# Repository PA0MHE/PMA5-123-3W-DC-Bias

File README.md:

# PMA5-123-3W--DC-Bias

 DC bias PCB for PMA5-123-3W MMIC 3W 10GHz
 - ATtiny412 SW controlled
 - LDO for VDD, typical 7V
 - Switch to switch off or on Vdd
 - Idd Current measurment
 - DAC controlled (negative) Vgg powersupply
 - Inputs:
	+8 .. 12V DC
	PTT
 - Outputs
	Vdd
	Vgg (-1.5 .. -0.75V

# Key components:

	Attiny412
	MIC29302
	R05C1TF05S-R
	INA168

 # SW
	
	Uses megatinyCore in boardmanager
	Chip: ATtiny412
	clock: 8 MHz internal
	Programmer: serialUPDI 230400 baud

 By pressing SW1 during Power-Up, Idq is set to ~400mA and stored in EEPROM
 	
 HEX file is included.

# PCB

Gerber files are included, PCB's can be ordered at JCL PCB 

# Software

A V1.0 of the Control software is included.

# Disclaimer  

"This software and hardware design is provided "as is" and without  
any warranties, express or implied, including but not limited to the   
implied warranties of merchantability and fitness for a particular purpose." 
	
Normal operation:
During RX the Vgg is at around -1.5V and the Vdd is zero.
In TX the for 400mA Idq required bias voltage is applied at Vgg
	
First time use / calibration:
When SW1 is pressed during power up, the Idq is aligned at ~400mA, the required Vgg value is stored in non volatile memory.
When this above calibration is not done, the a Vgg minimum value of ~ -1.5V is always applied.

73's

Maarten PA0MHE, Rens PA3AXA

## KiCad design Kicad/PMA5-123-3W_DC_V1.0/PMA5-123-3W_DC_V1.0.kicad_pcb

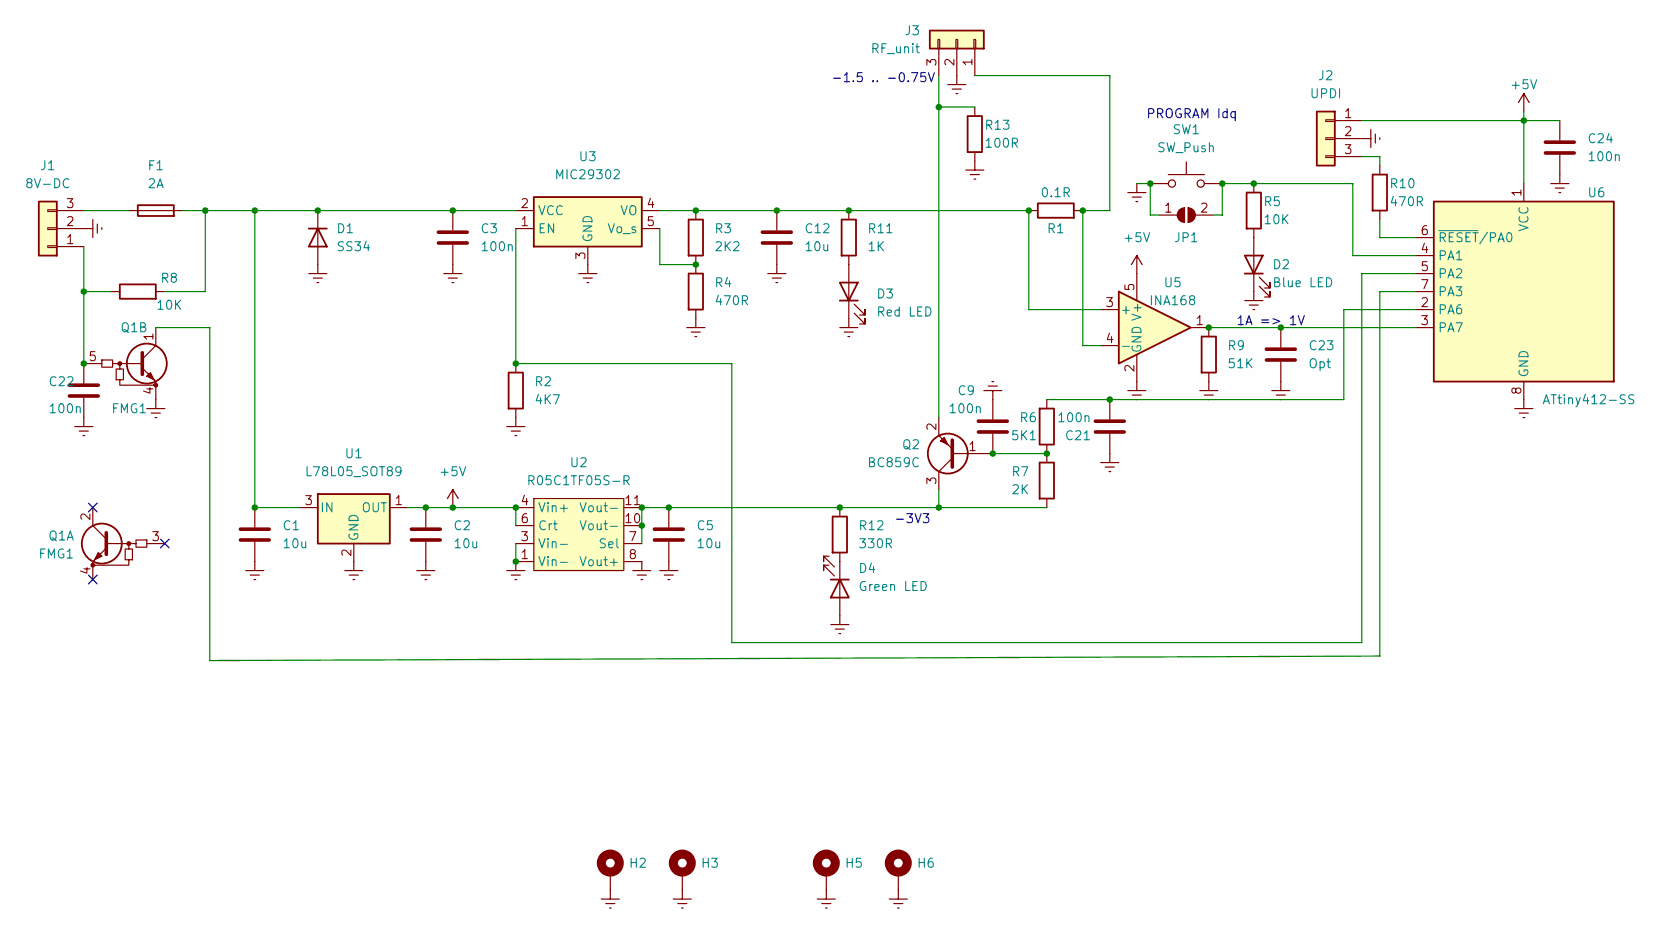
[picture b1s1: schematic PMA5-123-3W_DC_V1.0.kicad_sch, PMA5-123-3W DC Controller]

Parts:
C1: 10u; C_0805_2012Metric
C2, C5, C12: 10u; C_0603_1608Metric
C3, C9, C21, C22, C24: 100n; C_0603_1608Metric
C23: Opt; C_0603_1608Metric
D1: SS34; D_SMA; Mouser 750-SS34BF
D2: Blue LED; LED_0805_2012Metric
D3: Red LED; LED_0805_2012Metric
D4: Green LED; LED_0805_2012Metric
F1: 2A; Fuse_1812_4532Metric_Pad1.30x3.40mm_HandSolder; Mouser 576-1812L200/12DR
H2, H3, H5, H6: MountingHole_2.7mm_M2.5_Pad_Via
J1: 8V-DC; KF301-3P
J2: UPDI; PinHeader_1x03_P2.54mm_Vertical
J3: RF_unit; KF301-3P
JP1: '; SolderJumper-2_P1.3mm_Open_RoundedPad1.0x1.5mm
Q1: FMG1; SOT-25_HandSoldering; Mouser 755-FMG1AT148
Q2: BC859C; SOT-23
R1: 0.1R; R_2512_6332Metric; Mouser 603-PT2512FK-070R1L
R2: 4K7; R_0603_1608Metric
R3: 2K2; R_0603_1608Metric
R4, R10: 470R; R_0603_1608Metric
R5, R8: 10K; R_0603_1608Metric
R6: 5K1; R_0603_1608Metric
R7: 2K; R_0603_1608Metric
R9: 51K; R_0603_1608Metric
R11: 1K; R_0603_1608Metric
R12: 330R; R_0603_1608Metric
R13: 100R; R_0805_2012Metric
SW1: SW_Push; SW_SPST_FSMSM
U1: L78L05_SOT89; SOT-89-3; Mouser 511-L78L05ABU
U2: R05C1TF05S-R; R05C1TF05S; Mouser 919-R05C1TF05S-R
U3: MIC29302; TO-263-5_TabPin3; Mouser 998-MIC29302WU
U5: INA168; SOT-23-5; Mouser 595-INA168NA/3K
U6: ATtiny412-SS; SOIC-8_3.9x4.9mm_P1.27mm; Mouser 579-ATTINY412-SSF

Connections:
+5V: C2.1, C24.1, J2.1, U1.1 (OUT), U2.4 (Vin+), U2.5 (Vin+), U2.6 (Crt), U5.5 (V+), U6.1 (VCC)
GNDREF: C1.2, C2.2, C3.2, C5.2, C9.1, C12.2, C21.1, C22.2, C23.2, C24.2, D1.2 (A), D2.1 (K), D3.1 (K), D4.2 (A), H2.1, H3.1, H5.1, H6.1, J1.2, J2.2, J3.2, JP1.1 (A), Q1.4 (E1), R2.2, R4.2, R9.2, R13.2, SW1.1, U1.2 (GND), U2.1 (Vin-), U2.2 (Vin-), U2.3 (Vin-), U2.8 (Vout+), U2.9 (Vout+), U3.3 (GND), U5.2 (GND), U6.8 (GND)
unnamed: C1.1, C3.1, D1.1 (K), F1.2, R8.2, U1.3 (IN), U3.2 (VCC)
unnamed: C5.1, Q2.3 (C), R7.2, R12.1, U2.7 (Sel), U2.10 (Vout-), U2.11 (Vout-), U2.12 (Vout-)
unnamed: C9.2, Q2.1 (B), R6.1, R7.1
unnamed: C12.1, R1.1, R3.1, R11.1, U3.4 (VO), U5.3 (+)
unnamed: C21.2, R6.2, U6.2 (PA6)
unnamed: C22.1, J1.1, Q1.5 (B1), R8.1
unnamed: C23.1, R9.1, U5.1, U6.3 (PA7)
unnamed: D2.2 (A), R5.2
unnamed: D3.2 (A), R11.2
unnamed: D4.1 (K), R12.2
unnamed: F1.1, J1.3
unnamed: J2.3, R10.1
unnamed: J3.1, R1.2, U5.4 (-)
unnamed: J3.3, Q2.2 (E), R13.1
unnamed: JP1.2 (B), R5.1, SW1.2, U6.4 (PA1)
unnamed: Q1.1 (C1), U6.7 (PA3)
unnamed: R2.1, U3.1 (EN), U6.5 (PA2)
unnamed: R3.2, R4.1, U3.5 (Vo_s)
unnamed: R10.2, U6.6 (~RESET/PA0)

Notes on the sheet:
PROGRAM Idq
-3V3
-1.5 .. -0.75V
1A => 1V

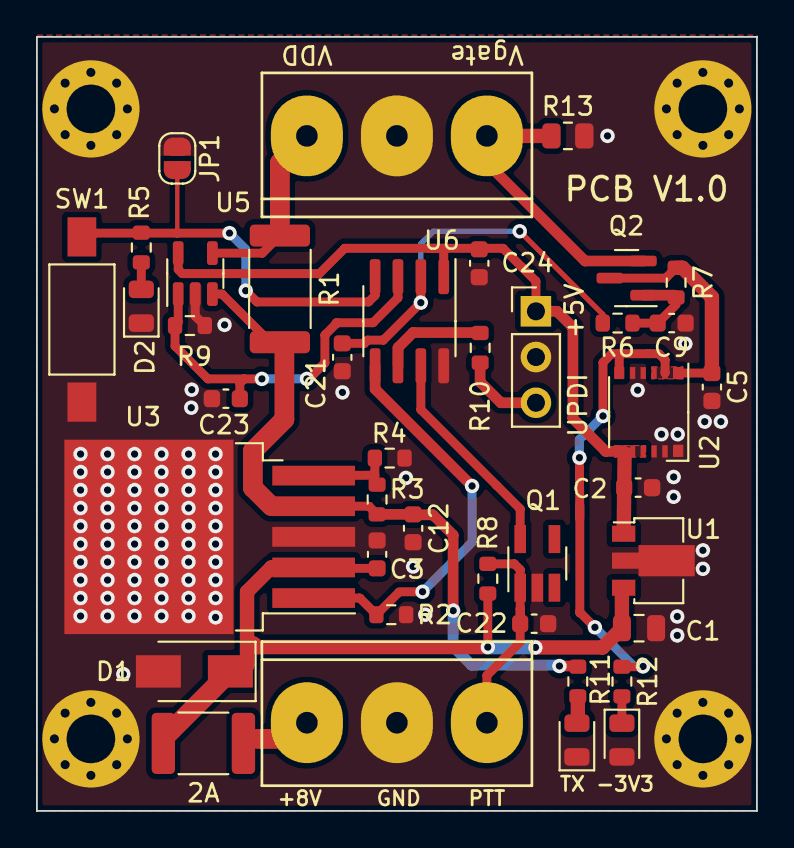
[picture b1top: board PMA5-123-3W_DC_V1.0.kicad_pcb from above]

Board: 2 copper layers, 40.0 x 43.0 mm, 44 parts (0 on the bottom side), 21 nets.

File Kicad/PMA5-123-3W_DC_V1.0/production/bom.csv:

Designator,Footprint,Quantity,Value,LCSC Part #
C1,0805,1,10u,
"C12, C2, C5",0603,3,10u,
"C21, C22, C24, C3, C9",0603,5,100n,
C23,0603,1,Opt,
D1,D_SMA,1,SS34,
D2,0805,1,Blue LED,
D3,0805,1,Red LED,
D4,0805,1,Green LED,
F1,1812,1,2A,
"H2, H3, H5, H6",MountingHole_2.7mm_M2.5_Pad_Via,4,~,
J1,KF301-3P,1,8V-DC,
J2,PinHeader_1x03_P2.54mm_Vertical,1,UPDI,
J3,KF301-3P,1,RF_unit,
JP1,SolderJumper-2_P1.3mm_Open_RoundedPad1.0x1.5mm,1,',
Q1,SOT-25_HandSoldering,1,FMG1,
Q2,SOT-23,1,BC859C,
R1,2512,1,0.1R,
"R10, R4",0603,2,470R,
R11,0603,1,1K,
R12,0603,1,330R,
R13,0805,1,100R,
R2,0603,1,4K7,
R3,0603,1,2K2,
"R5, R8",0603,2,10K,
R6,0603,1,5K1,
R7,0603,1,2K,
R9,0603,1,51K,
SW1,SW_SPST_FSMSM,1,SW_Push,
U1,SOT-89-3,1,L78L05_SOT89,
U2,R05C1TF05S,1,R05C1TF05S-R,
U3,TO-263-5_TabPin3,1,MIC29302,
U5,SOT-23-5,1,INA168,
U6,SOIC-8_3.9x4.9mm_P1.27mm,1,ATtiny412-SS,

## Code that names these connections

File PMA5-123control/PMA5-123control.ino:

/* DC control Minicircuit PMA5-123-3W+ 3W 10GHz GaAs MMIC
 *  
 * Maarten PA0MHE
 * 
 * 31-03-2025
 * 
 */


#define pttPin     PIN_PA3 // package pin 7 on AtTiny 412
#define vddEnable  PIN_PA2 // package pin 5
#define currADC    PIN_PA7 // package pin 3
#define switchPin  PIN_PA1 // package pin 4
#define VgateDAC   PIN_PA6 // DAC It must be package pin 2

#define VgateMin 0 // DAC value for lowest Vgate useally -1.5V
#define VgateTarget 100 //
#define VgateMax 255 // DAC value for highest Vgate -0.4V
#define targetCurrent 400 // 51K 10x, 500 =~ 1.2A 400=~1A
#define currMax  1000  // 2.4A
#define delaySteps 10

bool TX = false;
bool error = false;

int stabVgate =VgateMin;

void setup()
{
  digitalWrite(vddEnable, LOW);   // 7V VDD of PMA5-123 is OFF 
  pinMode(vddEnable, OUTPUT);

  DACReference(INTERNAL4V3);
  analogReference(INTERNAL2V5);  

  pinMode(pttPin, INPUT_PULLUP);
  pinMode(switchPin, INPUT_PULLUP);
  
  analogWrite(VgateDAC, VgateMin);
  
  delay(4000);
  analogRead(currADC);
}

  

void loop() {
//VGateTest(0,255);

// NormalControl();

// StabControl();

 FixedVggControl(VgateTarget);

 } // End loop


void StabControl(void) { 
  if (analogRead(currADC) > currMax) {
   error = true;
   SwitchOffPA();
  }
  if (!error) StabCurrent(targetCurrent);
}


void NormalControl(void) {
  if (analogRead(currADC) > currMax) {
   error = true;
   SwitchOffPA();
  }
  if (!error) {
     if (digitalRead(pttPin)) { // RX mode
        if (TX) SwitchOffPA();
      }
      else {    // TX mode
        if (!TX) {
          if (SwitchOnPA()) TX=true; 
          }
       }  
    }
}


bool SwitchOnPA(void) {
  analogWrite(VgateDAC, VgateMin);
  delay(delaySteps); 
  digitalWrite(vddEnable, HIGH);   // 7V VDD of PMA5-123 is ON 
  for (int i=VgateMin; i < VgateMax; i++) {
    if (i == VgateMax -1) {
      error = true;
      return false;
    }
    analogWrite(VgateDAC, i);
    delay(delaySteps);   
    if (analogRead(currADC) > targetCurrent) {
      return true;
    }
  }
}


void SwitchOffPA(void) {
  digitalWrite(vddEnable, LOW);   // 7V VDD of PMA5-123 is OFF 
  analogWrite(VgateDAC, VgateMin);
  TX = false;
}


void FixedVggControl(int Vgg) {
  analogWrite(VgateDAC, Vgg);
  if (analogRead(currADC) > currMax) {
   error = true;
   digitalWrite(vddEnable, LOW);   // 7V VDD of PMA5-123 is OFF 
  }
  if (!error) {
     if (digitalRead(pttPin)) { // RX mode
        if (TX) digitalWrite(vddEnable, LOW);   // 7V VDD of PMA5-123 is OFF 
      }
      else {    // TX mode
        if (!TX) {
          digitalWrite(vddEnable, HIGH);   // 7V VDD of PMA5-123 is ON
          TX=true; 
          }
       }  
    }  
}

void StabCurrent(int cur) {
  digitalWrite(vddEnable, HIGH);   // 7V VDD of PMA5-123 is ON 
  if (analogRead(currADC) < cur -2) {
    stabVgate = stabVgate+1;
  }
    if (analogRead(currADC) > cur +2) {
    stabVgate =stabVgate-1;
  }
      analogWrite(VgateDAC,stabVgate );
}


void VGateTest(int minV, int maxV) {
  digitalWrite(vddEnable, LOW);   // PMA5-123 is OFF 
  analogWrite(VgateDAC, maxV);
  delay(4000);
  analogWrite(VgateDAC, minV);
  delay(4000);
}

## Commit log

2025-04-18 Used right symbol in schematic
2025-05-05 Update Kicad and SW
2025-05-05 Create PMA5-123-3#_withBiasCircuit.jpg
    Added picture
2025-05-05 Update PMA5-123control.ino
    Changed EEprom initialization
2025-05-06 Create PMA5-123control.ino.t412.8c0.mD0.v2610.hex
    Added HEX file
2025-05-15 Changed symbol Q2
2025-05-15 Changed value
2025-05-16 Added R13 and JP1
2025-06-01 Kicad closed update
2025-06-01 Remove Kicad BackUp Files
2025-06-01 Removed .dot file
2025-06-02 added calibration in readme
